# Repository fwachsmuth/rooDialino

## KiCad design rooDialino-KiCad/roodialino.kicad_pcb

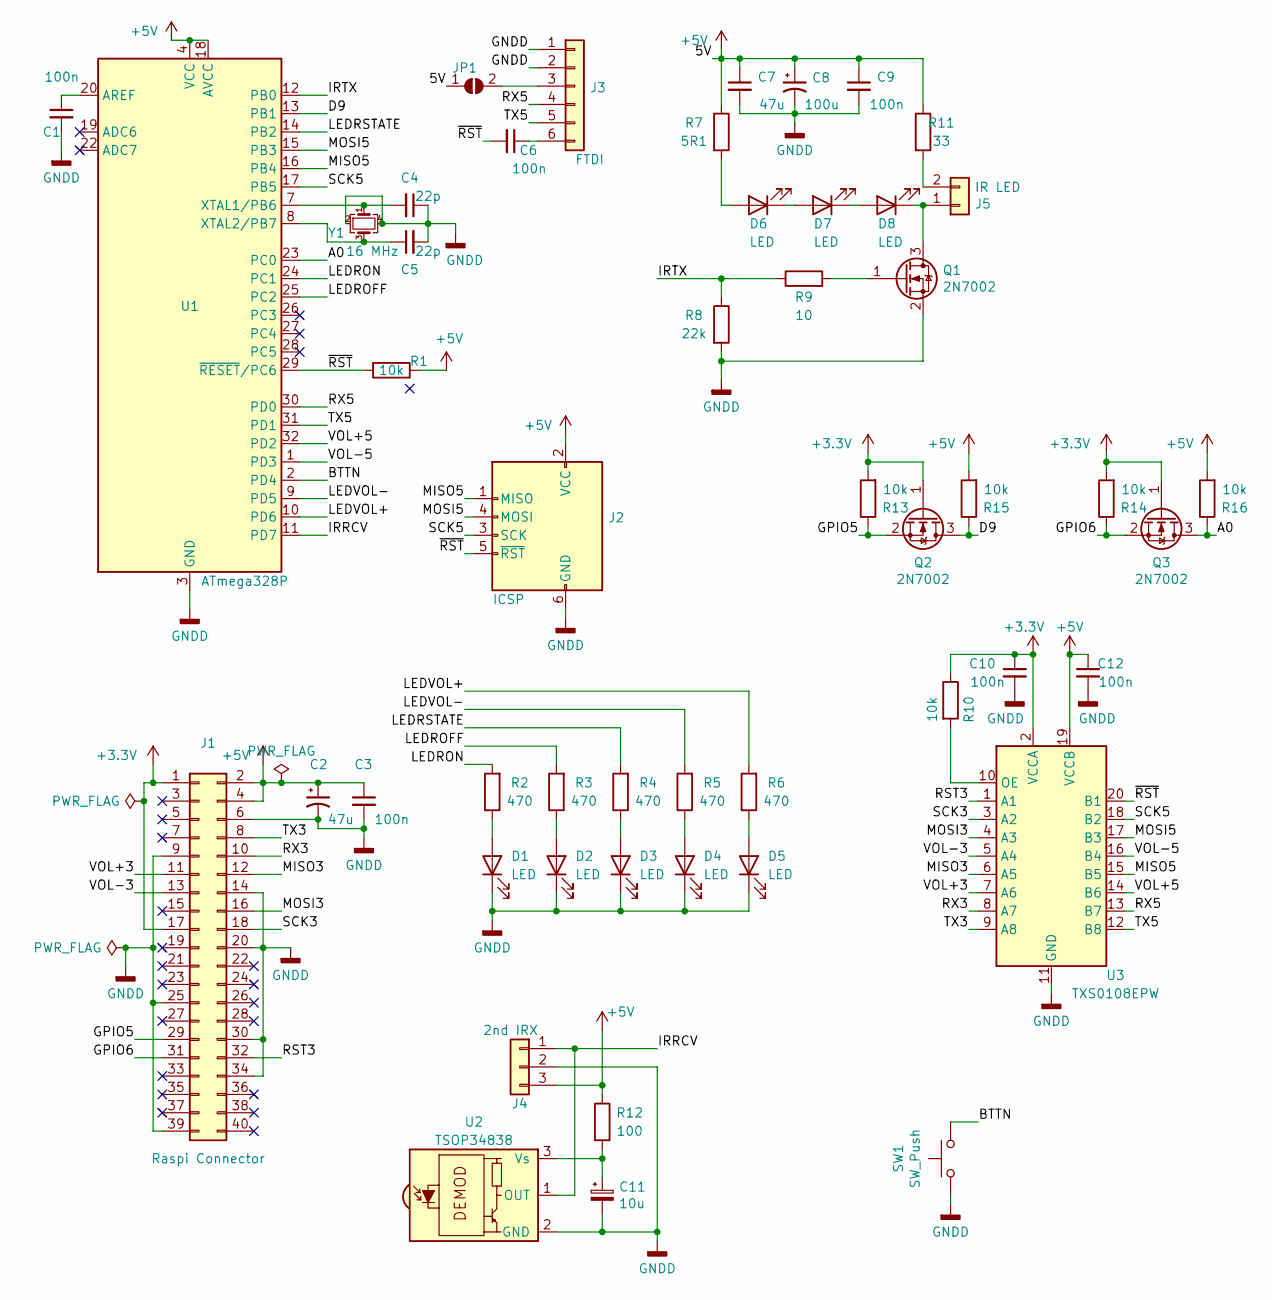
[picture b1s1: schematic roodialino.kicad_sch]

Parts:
C1: 100n; C_0603_1608Metric; LCSC C14663
C2: 47u; CP_Elec_4x5.8; LCSC C178589
C3, C6, C9, C10, C12: 100n; C_0402_1005Metric; LCSC C1525
C4, C5: 22p; C_0402_1005Metric; LCSC C1555
C7: 47u; C_1206_3216Metric; LCSC C15008
C8: 100u; CP_Elec_4x5.8; LCSC C178589
C11: 10u; CP_EIA-3216-18_Kemet-A; LCSC C7171
D1, D2, D3: LED; LED_0603_1608Metric; LCSC C72041
D4: LED; LED_0603_1608Metric; LCSC C72038
D5: LED; LED_0603_1608Metric; LCSC C72043
D6, D8: LED; LED_D5.0mm_Horizontal_O1.27mm_Z3.0mm_IRBlack; LCSC C55528
D7: LED; LED_D5.0mm_IRBlack; LCSC C55528
J1: Raspi Connector; PinSocket_2x20_P2.54mm_Vertical
J2: ICSP; PinHeader_2x03_P2.54mm_Vertical
J3: FTDI; PinHeader_1x06_P2.54mm_Vertical
J4: 2nd IRX; PinHeader_1x03_P2.54mm_Vertical
J5: IR LED; PinHeader_1x02_P2.54mm_Vertical
JP1: SolderJumper_2_Open; SolderJumper-2_P1.3mm_Open_RoundedPad1.0x1.5mm
Q1, Q2, Q3: 2N7002; SOT-23; LCSC C8545
R1, R10, R13, R14, R15, R16: 10k; R_0402_1005Metric; LCSC C25744
R2, R3, R4, R5, R6: 470; R_0402_1005Metric; LCSC C25117
R7: 5R1; R_0805_2012Metric; LCSC C17724
R8: 22k; R_0402_1005Metric
R9: 10; R_0402_1005Metric
R11: 33; R_0603_1608Metric; LCSC C23140
R12: 100; R_0402_1005Metric; LCSC C25076
SW1: SW_Push; SW_SPST_TL3342; LCSC C318884
U1: ATmega328P; TQFP-32_7x7mm_P0.8mm; LCSC C14877
U2: TSOP34838; Vishay_MOLD-3Pin; LCSC C44620
U3: TXS0108EPW; TSSOP-20_4.4x6.5mm_P0.65mm; LCSC C17206
Y1: 16 MHz; Crystal_SMD_3225-4Pin_3.2x2.5mm; LCSC C13738

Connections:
+3V3: C10.1, J1.1, J1.17, Q2.1 (G), Q3.1 (G), R10.1, R13.2, R14.2, U3.2 (VCCA)
+5V: C2.1, C3.1, C7.1, C8.1, C9.1, C12.1, J1.2, J1.4, J2.2 (VCC), J4.3, JP1.1 (A), R1.1, R7.1, R11.1, R12.1, R15.2, R16.2, U1.4 (VCC), U1.6 (VCC), U1.18 (AVCC), U3.19 (VCCB)
/A0: Q3.3 (D), R16.1, U1.23 (PC0)
/BTTN: SW1.2, U1.2 (PD4)
/D9: Q2.3 (D), R15.1, U1.13 (PB1)
/GPIO5: J1.29, Q2.2 (S), R13.1
/GPIO6: J1.31, Q3.2 (S), R14.1
/IRRCV: J4.1, U1.11 (PD7), U2.1 (OUT)
/IRTX: R8.1, R9.1, U1.12 (PB0)
/LEDROFF: R3.2, U1.25 (PC2)
/LEDRON: R2.2, U1.24 (PC1)
/LEDRSTATE: R4.2, U1.14 (PB2)
/LEDVOL+: R6.2, U1.10 (PD6)
/LEDVOL-: R5.2, U1.9 (PD5)
/MISO3: J1.12, U3.6 (A5)
/MISO5: J2.1 (MISO), U1.16 (PB4), U3.15 (B5)
/MOSI3: J1.16, U3.4 (A3)
/MOSI5: J2.4 (MOSI), U1.15 (PB3), U3.17 (B3)
/RST3: J1.32, U3.1 (A1)
/RX3: J1.10, U3.8 (A7)
/RX5: J3.4, U1.30 (PD0), U3.13 (B7)
/SCK3: J1.18, U3.3 (A2)
/SCK5: J2.3 (SCK), U1.17 (PB5), U3.18 (B2)
/TX3: J1.8, U3.9 (A8)
/TX5: J3.5, U1.31 (PD1), U3.12 (B8)
/VOL+3: J1.11, U3.7 (A6)
/VOL+5: U1.32 (PD2), U3.14 (B6)
/VOL-3: J1.13, U3.5 (A4)
/VOL-5: U1.1 (PD3), U3.16 (B4)
/~RST~: C6.2, J2.5 (~RST), R1.2, U1.29 (~RESET/PC6), U3.20 (B1)
GNDD: C1.2, C2.2, C3.2, C4.1, C5.2, C7.2, C8.2, C9.2, C10.2, C11.2, C12.2, D1.1 (K), D2.1 (K), D3.1 (K), D4.1 (K), D5.1 (K), J1.6, J1.9, J1.14, J1.20, J1.25, J1.30, J1.34, J1.39, J2.6 (GND), J3.1, J3.2, J4.2, Q1.2 (S), R8.2, SW1.1, U1.3 (GND), U1.5 (GND), U1.21 (GND), U2.2 (GND), U3.11 (GND), Y1.2, Y1.4
unnamed: C1.1, U1.20 (AREF)
unnamed: C4.2, U1.7 (XTAL1/PB6), Y1.1
unnamed: C5.1, U1.8 (XTAL2/PB7), Y1.3
unnamed: C6.1, J3.6
unnamed: C11.1, R12.2, U2.3 (Vs)
unnamed: D1.2 (A), R2.1
unnamed: D2.2 (A), R3.1
unnamed: D3.2 (A), R4.1
unnamed: D4.2 (A), R5.1
unnamed: D5.2 (A), R6.1
unnamed: D6.1 (K), D7.2 (A)
unnamed: D6.2 (A), R7.2
unnamed: D7.1 (K), D8.2 (A)
unnamed: D8.1 (K), J5.1, Q1.3 (D)
unnamed: J3.3, JP1.2 (B)
unnamed: J5.2, R11.2
unnamed: Q1.1 (G), R9.2
unnamed: R10.2, U3.10 (OE)

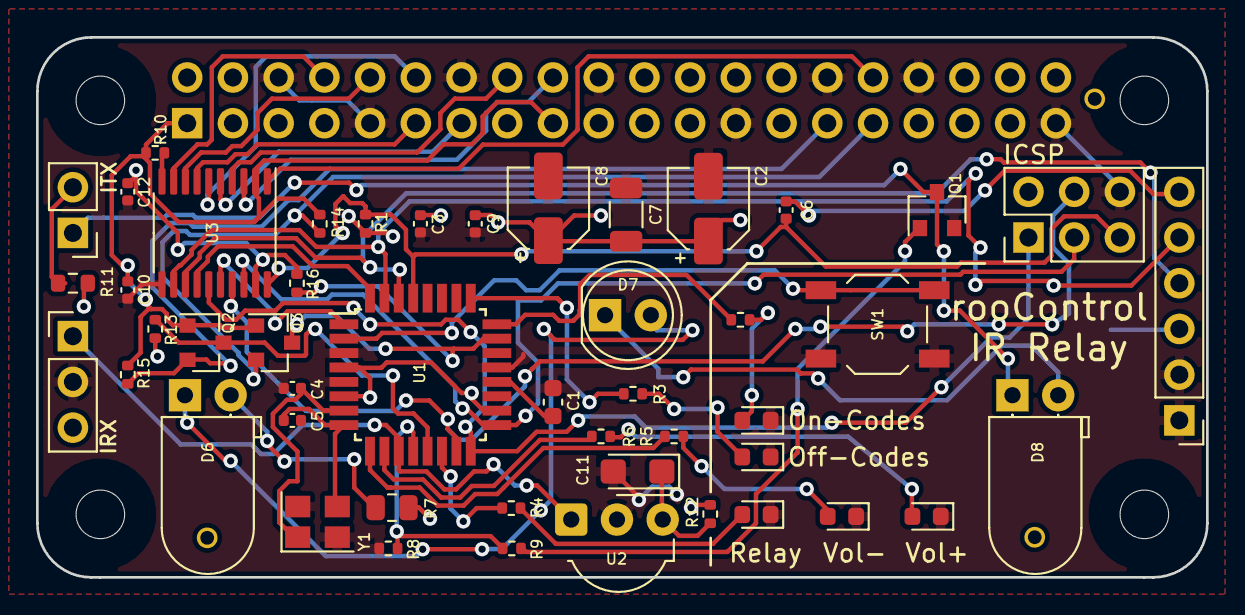
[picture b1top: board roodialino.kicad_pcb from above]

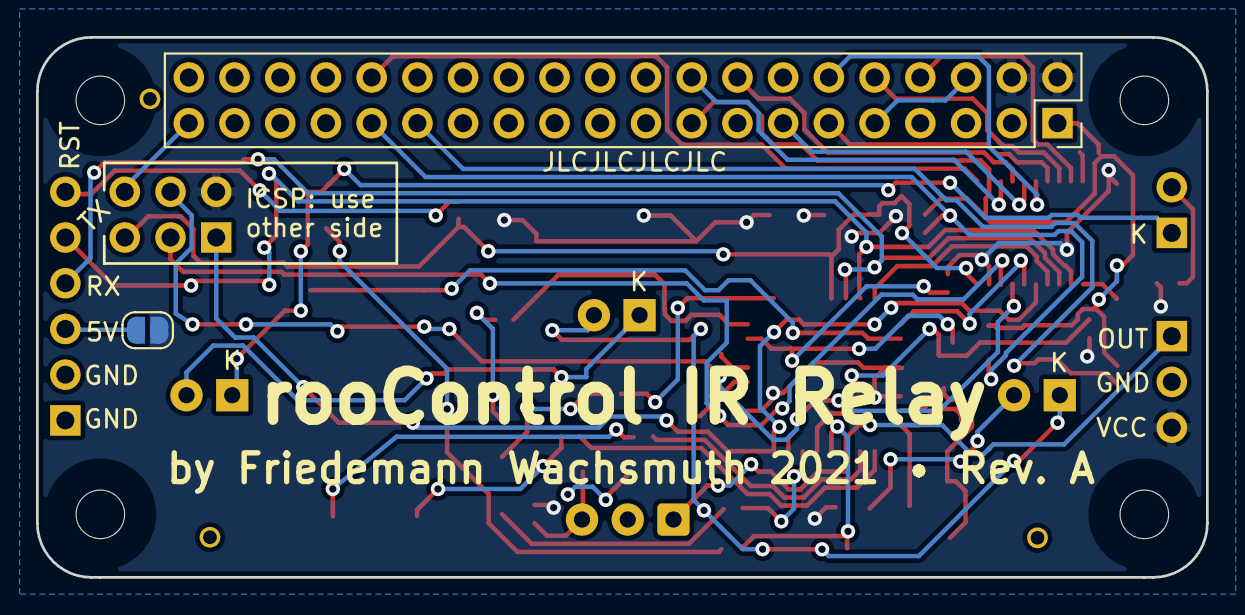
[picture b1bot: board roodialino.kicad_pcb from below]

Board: 2 copper layers, 65.0 x 30.0 mm, 54 parts (2 on the bottom side), 49 nets.

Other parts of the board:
H1, H2, H3, H4: MountingHole; MountingHole_2.7mm_M2.5_uHAT_RPi

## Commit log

2021-10-04 Moving Todos to github issues
2021-10-04 Adding some data sheets
2021-10-04 Fixing stupi pin naming
2021-10-04 Just adding a comment
2021-10-04 Fixing #5. No pulses are lost and we fire fast
2021-10-05 Starting to bring in Siluino funcs. Not copiling yet
2021-10-05 Compiling. Frankenstein State!
2021-10-05 remove deadbeef
2021-10-06 Adding State Machines that make sense. Cleaned up Siluino relics
2021-10-07 Scaffolding FSM, breaking down into missing pieces
2021-10-07 Cleaner FSM with dedicated transitionTo_FUNCTIONs. Also, fixes #6
2021-10-07 Cleanup
2021-10-07 Prepare for recording (storing) and scalable sending of IR codes
2021-10-08 Update README.md
    Adding the FSM UML PNG. Fsmumlpng!
2021-10-08 Widen usage of transition functions. Breaking things :)
2021-10-08 50% fixing the logic
2021-10-08 Struct wip
2021-10-08 Fixing #12: Fix learnIRCode() to learn multiple things: needs a 250ms wait, needs to write different structs (struct array)
2021-10-09 Fixes #14: Do not accept UNKNOWN Protocol when learning IR
2021-10-09 Small Cleanup
2021-10-09 Cleanup, working now, #16 still an issue
2021-10-09 Yet more cleanup but #16 remains -.-
2021-10-09 Fixes #18. Inverse roll-over problem happening while millis() was <3000
2021-10-09 Adding hints potentially solving #16
2021-10-09 Fixes #9: save codes to EEPROM
2021-10-09 fixes #8: read codes from EEPROM
2021-10-09 Fixes an embarrassing array index bug
2021-10-09 Validating that EEPROM-Reading works
2021-10-09 saving current working state before refactoring out the nested struct fo raw data (mem & brain eater)
2021-10-09 Gone with the nested struct
2021-10-09 Finally — selctive toggling works. Partially fixes #17
2021-10-11 Kalle findet Bugs!
2021-10-14 Freeing up SPI pins currently used by LEDs — just to avoid conflicts during programming
2021-10-14 Adding some Datasheets
2021-10-14 Adding KiCad WIP (Schematics only for now)
2021-10-14 More schematics
2021-10-15 Footprints completed
2021-10-15 More datasheets
2021-10-15 all parts placed on board
2021-10-16 More routing
2021-10-16 cash
2021-10-16 Nets complete!
2021-10-17 Looking good, that PCB
2021-10-18 First Gerber
2021-10-18 adding helpful URLs
2021-10-18 Fixing the crystal footprint
2021-10-19 Fixes on the PCB
2021-10-19 my first enum
2021-10-19 My first Debug Macro
2021-10-19 fixes #16
2021-10-19 enum for LED modes
2021-10-19 Better caps, less magic smoke!
2021-10-20 Removing debounce RC
2021-10-20 Tons of Trace Optimizations
2021-10-23 Levelshifter's OE gets permanently enabled. No need to ever have it low.
2021-10-23 Fixing IRX wiring, adding ESO protection
2021-10-23 Saving before i size down some 0805s
2021-10-23 Reroute to 0402 complete. Also, bugs fixed
2021-10-23 More bugfixes
2021-10-23 DRC complete
2021-10-23 Some final (?) bling
2021-10-23 Rev A ready to Order!
2021-10-24 Committing before adding serial support
2021-10-24 Serial Strawman
2021-10-24 Add Tooling Holes
2021-10-25 The RevA I actually ordered.
2021-10-25 kicad save
2021-10-25 Wrapped all Serial.prints into DEBUG macro, since we'll later need the serial for comms
2021-10-26 Updating R11 to 0603 footprint in the BOM. JLC won't populate it.
2021-10-26 Just notes in comments
2021-10-26 Going VSCode. Bye Bye crappy Processing IDE...
2021-10-26 LED Refactoring. Fixes #23 (with Todos) and prepares for two more LEDs
2021-10-26 Cleanup before going to bed
2021-10-27 Fixes Volume Direction, Sets Feedback LED back to normal once last IR pulse was sent
2021-10-27 Fixes #10 and #27
2021-10-27 minor cleanup and prep for more LEDs and Learn States
2021-10-28 Fixes #29
2021-10-29 Fixes #30
2021-10-29 Deleting old comments
2021-10-29 just adding curly brackets for a one line if
2021-10-29 Add Macro for better Debug Output Readbility
2021-10-29 Flush cached Vol-Changes when the Relay gets turned off
2021-10-29 First batch of Serial commands, as per #24
2021-10-29 Code Celanup, some LED prep work
2021-10-29 Setting us up for 5 LEDS and new blinkenmodes (quadruple and quintuple)
2021-10-29 beautified
2021-10-30 Refactoring of updateLeds() in progress (kadiwa)
2021-10-30 Fixing old updateLeds()
2021-10-30 Small bugfixes
2021-10-30 Refactored updateLeds() fn — thanks, kadiwa!
2021-10-30 add State enum
2021-10-30 ignore build folder
2021-10-30 Minor cleanup
2021-10-30 Calculating blink offste, to never start bliking in the middle of a repetitive cycle
2021-10-30 Restore Fastblink for Learning
2021-10-31 Fixes Vol Down/Up Learn Order; Fixes Skip-per-Button Inconsistency; Add sLearning of two more (single) codes
2023-11-20 Uncommited Gruscht
2023-11-20 Removing kicad backup garbage

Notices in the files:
rooDialino-KiCad/roodialino.kicad_pcb:
This PCB design is licensed under MIT Open Source License.
